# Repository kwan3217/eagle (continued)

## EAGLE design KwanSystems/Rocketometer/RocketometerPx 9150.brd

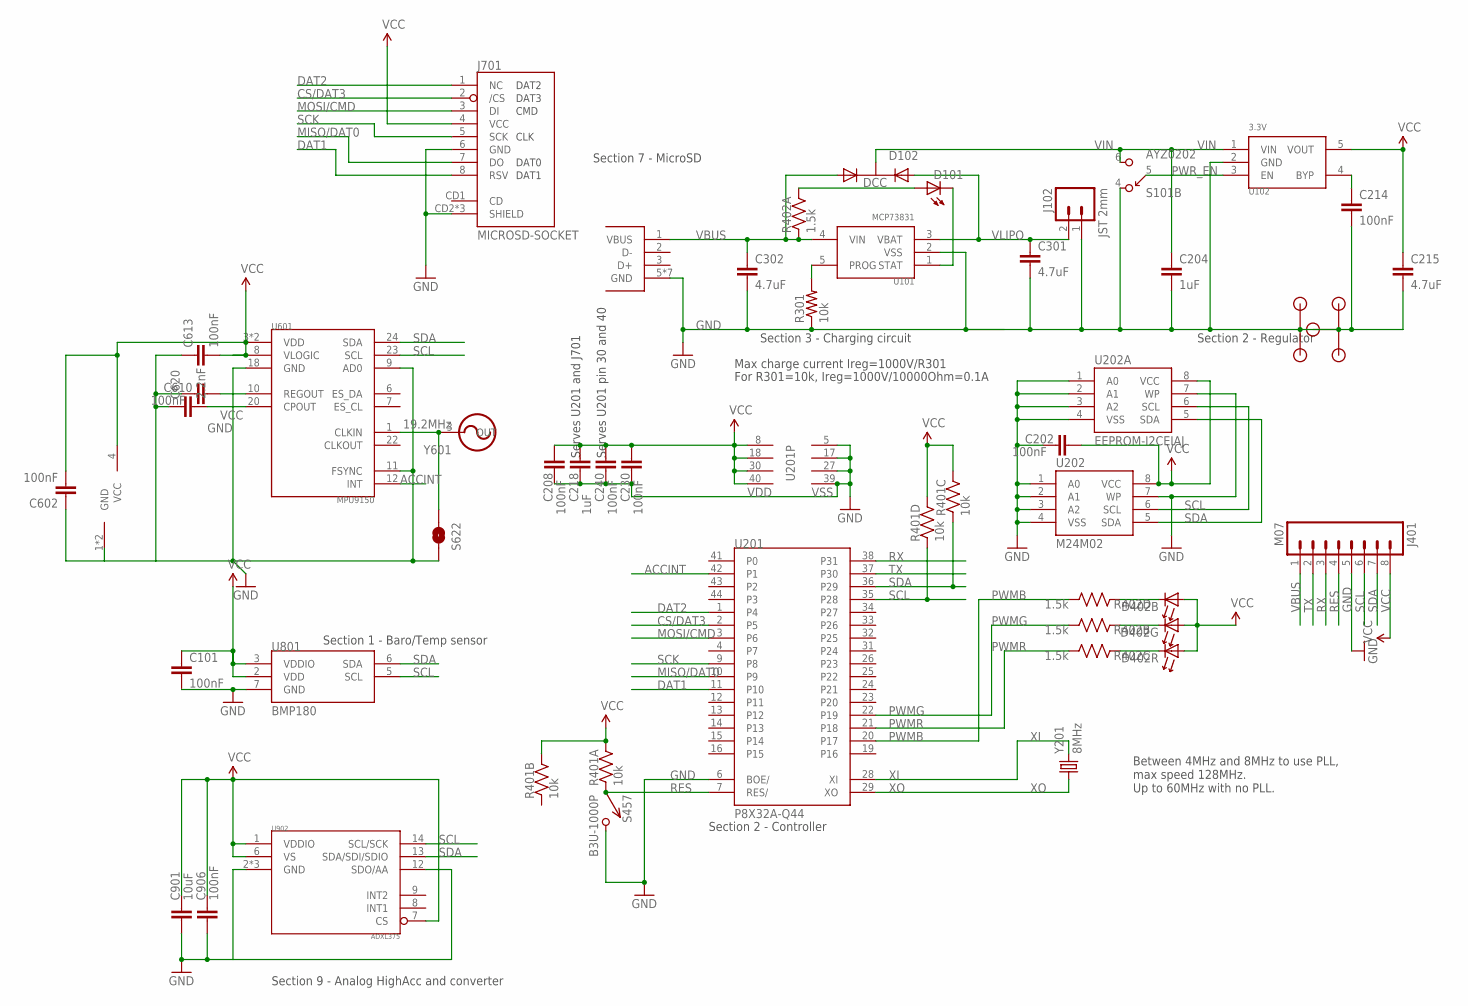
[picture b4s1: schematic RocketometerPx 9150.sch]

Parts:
C101, C202, C208, C214, C230, C240, C602, C610, C613: 100nF; 0402-CAP; DIGIKEY 445-1265-1-ND
C204, C218: 1uF; 0402-CAP; DIGIKEY 445-4114-1-ND
C215, C301, C302: 4.7uF; 0402-CAP; DIGIKEY 445-7395-1-ND
C620: 2.2nF; 0402-CAP; DIGIKEY 445-1257-1-ND
C901: 10uF; 0603-CAP; DIGIKEY 445-7486-1-ND
C906: 100nF; 0402-CAP; DIGIKEY 445-1317-2-ND
D101: YELLOW; LED-0603; DIGIKEY 350-2032-1-ND
D102: DCC; SOT-23-3; DIGIKEY 568-6500-1-ND
D402: SMLP36RGB2W(R); SMLP36
J101: USB_MICROB_JSTGCT; USB_MICROB_3075; DIGIKEY 455-2562-1-ND
J102: JST 2mm; JST-2-SMD; DIGIKEY 455-1749-1-ND
J401: M07; 1X08; DIGIKEY $NOPART
J701: MICROSD-SOCKET; MICROSD-SOCKET-PP; DIGIKEY 101-00581-59-1-ND
JP1, JP2, JP3, JP4, JP5: STANDOFF; DIGIKEY $NOPART
R301: 10k; 0402-RES; DIGIKEY P10.0KLCT-ND
R401: 10k; CRA04; DIGIKEY CRA4S810KCT-ND
R402: 1.5k; CRA04; DIGIKEY CRA4S81.5KCT-ND
S101: AYZ0202; DIGIKEY 401-2013-1-ND
S457: B3U-1000P; DIGIKEY SW1020CT-ND
S622: SOLDERJUMPERNO; SJ_2S-NO; DIGIKEY $NOPART
U101: MCP73831; SOT-23-5; DIGIKEY 576-1910-1-ND
U102: 3.3V; SOT-23-5; DIGIKEY 576-1910-1-ND
U201: P8X32A-Q44; DIGIKEY P8X32A-Q44-ND
U202: M24M02; SO8N; DIGIKEY 497-11600-1-ND
U202A: EEPROM-I2CEIAJ; SO08-EIAJ; DIGIKEY $NOPART
U601: MPU9150; MPU60X0; DIGIKEY $NOPART
U801: BMP180; DIGIKEY 828-1027-1-ND
U902: ADXL375
Y201: 8MHz; CRYSTAL_SMD_3_2MM_2_5MM; DIGIKEY 644-1178-1-ND
Y601: 19.2MHz; CRYSTAL_SMD_5MM_3_2MM

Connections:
ACCINT: U201.42 (P1), U601.12 (INT)
CS/DAT3: J701.2 (/CS), U201.2 (P5)
DAT1: J701.8 (RSV), U201.11 (P10)
DAT2: J701.1 (NC), U201.1 (P4)
GND: C101.2, C202.2, C204.2, C208.2, C214.2, C215.2, C218.2, C230.2, C240.2, C301.2, C302.2, C602.1, C610.2, C613.1, C620.1, C901.2, C906.2, J101.5 (GND), J101.P$1 (GND), J101.P$2 (GND), J101.P$3 (GND), J101.P$4 (GND), J101.P$8 (GND), J101.P$10 (GND), J102.1, J401.5, J701.6 (GND), J701.CD2 (SHIELD), J701.GND1 (SHIELD), J701.GND3 (SHIELD), JP1.P$1, JP2.P$1, JP3.P$1, JP4.P$1, JP5.P$1, R301.1, S101.4, S457.P$2 (2), S622.2, U101.2 (VSS), U102.2 (GND), U201.5 (VSS), U201.6 (BOE/), U201.17 (VSS), U201.27 (VSS), U201.39 (VSS), U202.1 (A0), U202.2 (A1), U202.3 (A2), U202.4 (VSS), U202.7 (WP), U202A.1 (A0), U202A.2 (A1), U202A.3 (A2), U202A.4 (VSS), U202A.7 (WP), U601.9 (AD0), U601.11 (FSYNC), U601.18 (GND), U801.7 (GND), U902.2 (GND), U902.4 (GND), U902.5 (GND), U902.12 (SDO/AA), Y601.1 (GND), Y601.2 (GND)
MISO/DAT0: J701.7 (DO), U201.10 (P9)
MOSI/CMD: J701.3 (DI), U201.3 (P6)
unnamed: C620.2, U601.20 (CPOUT)
unnamed: R301.2, U101.5 (PROG)
unnamed: S622.1, U601.1 (CLKIN), Y601.3 (OUT)
unnamed: D101.C, U101.1 (STAT)
unnamed: D101.A, R402.8 (2)
unnamed: C610.1, U601.10 (REGOUT)
unnamed: C214.1, U102.4 (BYP)
PWMB: R402.4 (1), U201.20 (P17)
PWMG: R402.2 (1), U201.22 (P19)
PWMR: R402.3 (1), U201.21 (P18)
PWR_EN: S101.5, U102.3 (EN)
QWMB: D402.3 (C), R402.6 (2)
QWMG: D402.5 (C), R402.7 (2)
QWMR: D402.1 (C), R402.5 (2)
RES: J401.4, R401.1, S457.P$1 (1), U201.7 (RES/)
RX: J401.3, U201.38 (P31)
SCK: J701.5 (SCK), U201.9 (P8)
SCL: J401.6, R401.4 (1), U201.35 (P28), U202.6 (SCL), U202A.6 (SCL), U601.23 (SCL), U801.5 (SCL), U902.14 (SCL/SCK)
SDA: J401.7, R401.3 (1), U201.36 (P29), U202.5 (SDA), U202A.5 (SDA), U601.24 (SDA), U801.6 (SDA), U902.13 (SDA/SDI/SDIO)
TX: J401.2, U201.37 (P30)
VBUS: C302.1, D102.1 (A1), J101.1 (VBUS), J401.1, R402.1, U101.4 (VIN)
VCC: C101.1, C202.1, C208.1, C215.1, C218.1, C230.1, C240.1, C602.2, C613.2, C901.1, C906.1, D402.2 (A), D402.4 (A), D402.6 (A), J401.8, J701.4 (VCC), R401.5 (2), R401.6 (2), R401.7 (2), R401.8 (2), U102.5 (VOUT), U201.8 (VDD), U201.18 (VDD), U201.30 (VDD), U201.40 (VDD), U202.8 (VCC), U202A.8 (VCC), U601.3 (VDD), U601.8 (VLOGIC), U601.13 (VDD), U801.2 (VDD), U801.3 (VDDIO), U902.1 (VDDIO), U902.6 (VS), U902.7 (CS), Y601.4 (VCC)
VIN: C204.1, D102.3 (K), S101.6, U102.1 (VIN)
VLIPO: C301.1, D102.2 (A2), J102.2, U101.3 (VBAT)
XI: U201.28 (XI), Y201.2
XO: U201.29 (XO), Y201.1

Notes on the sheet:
Section 2 - Regulator
Section 3 - Charging circuit
Section 7 - MicroSD
Section 1 - Baro/Temp sensor
Max charge current Ireg=1000V/R301
For R301=10k, Ireg=1000V/10000Ohm=0.1A
Section 2 - Controller
Serves U201 and J701
Serves U201 pin 30 and 40
Between 4MHz and 8MHz to use PLL, max speed 128MHz. Up to 60MHz with no PLL.
Section 9 - Analog HighAcc and converter

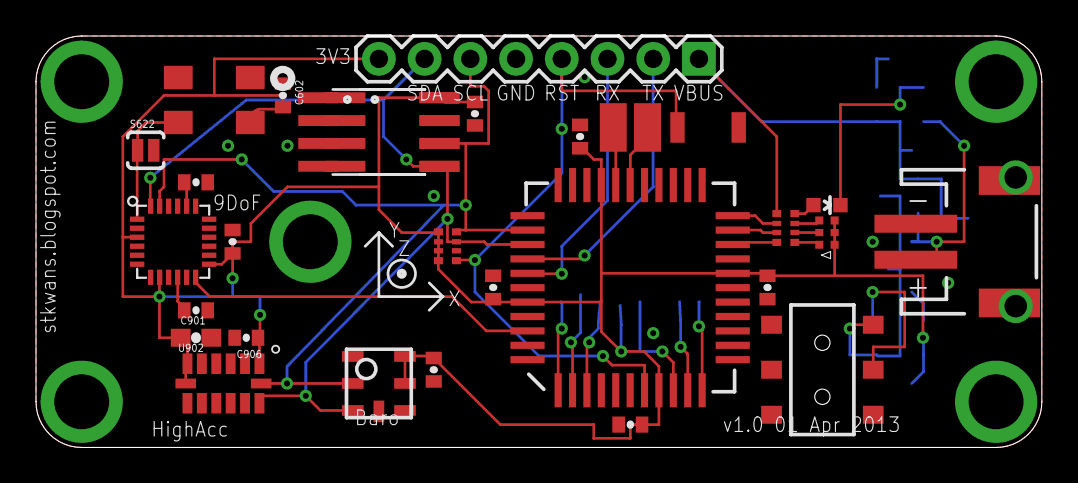
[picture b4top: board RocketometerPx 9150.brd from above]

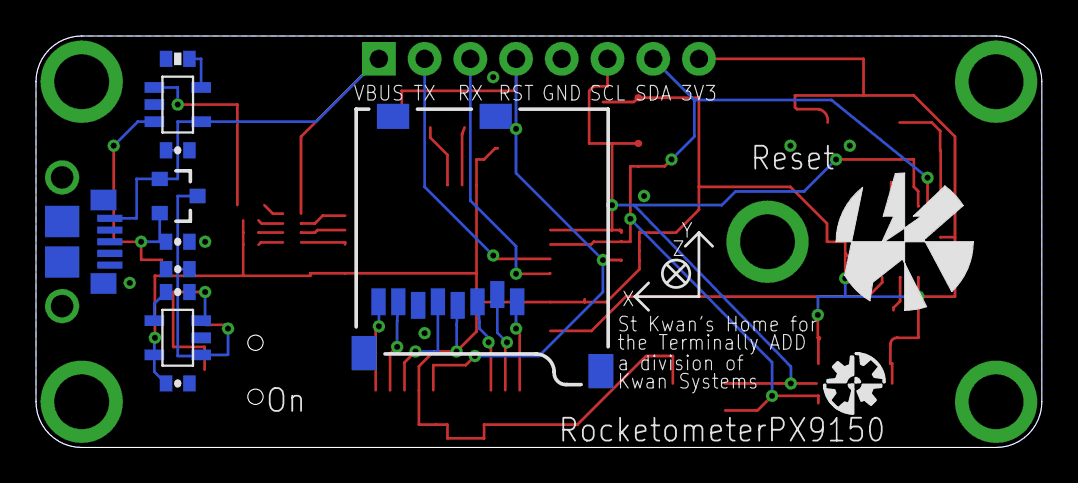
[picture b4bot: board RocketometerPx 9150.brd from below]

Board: 2 copper layers, 55.9 x 22.9 mm, 48 parts (13 on the bottom side), 33 nets.

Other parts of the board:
U$4: AXES
U$5: KWAN_ACC
U$6: OSHW_ACC

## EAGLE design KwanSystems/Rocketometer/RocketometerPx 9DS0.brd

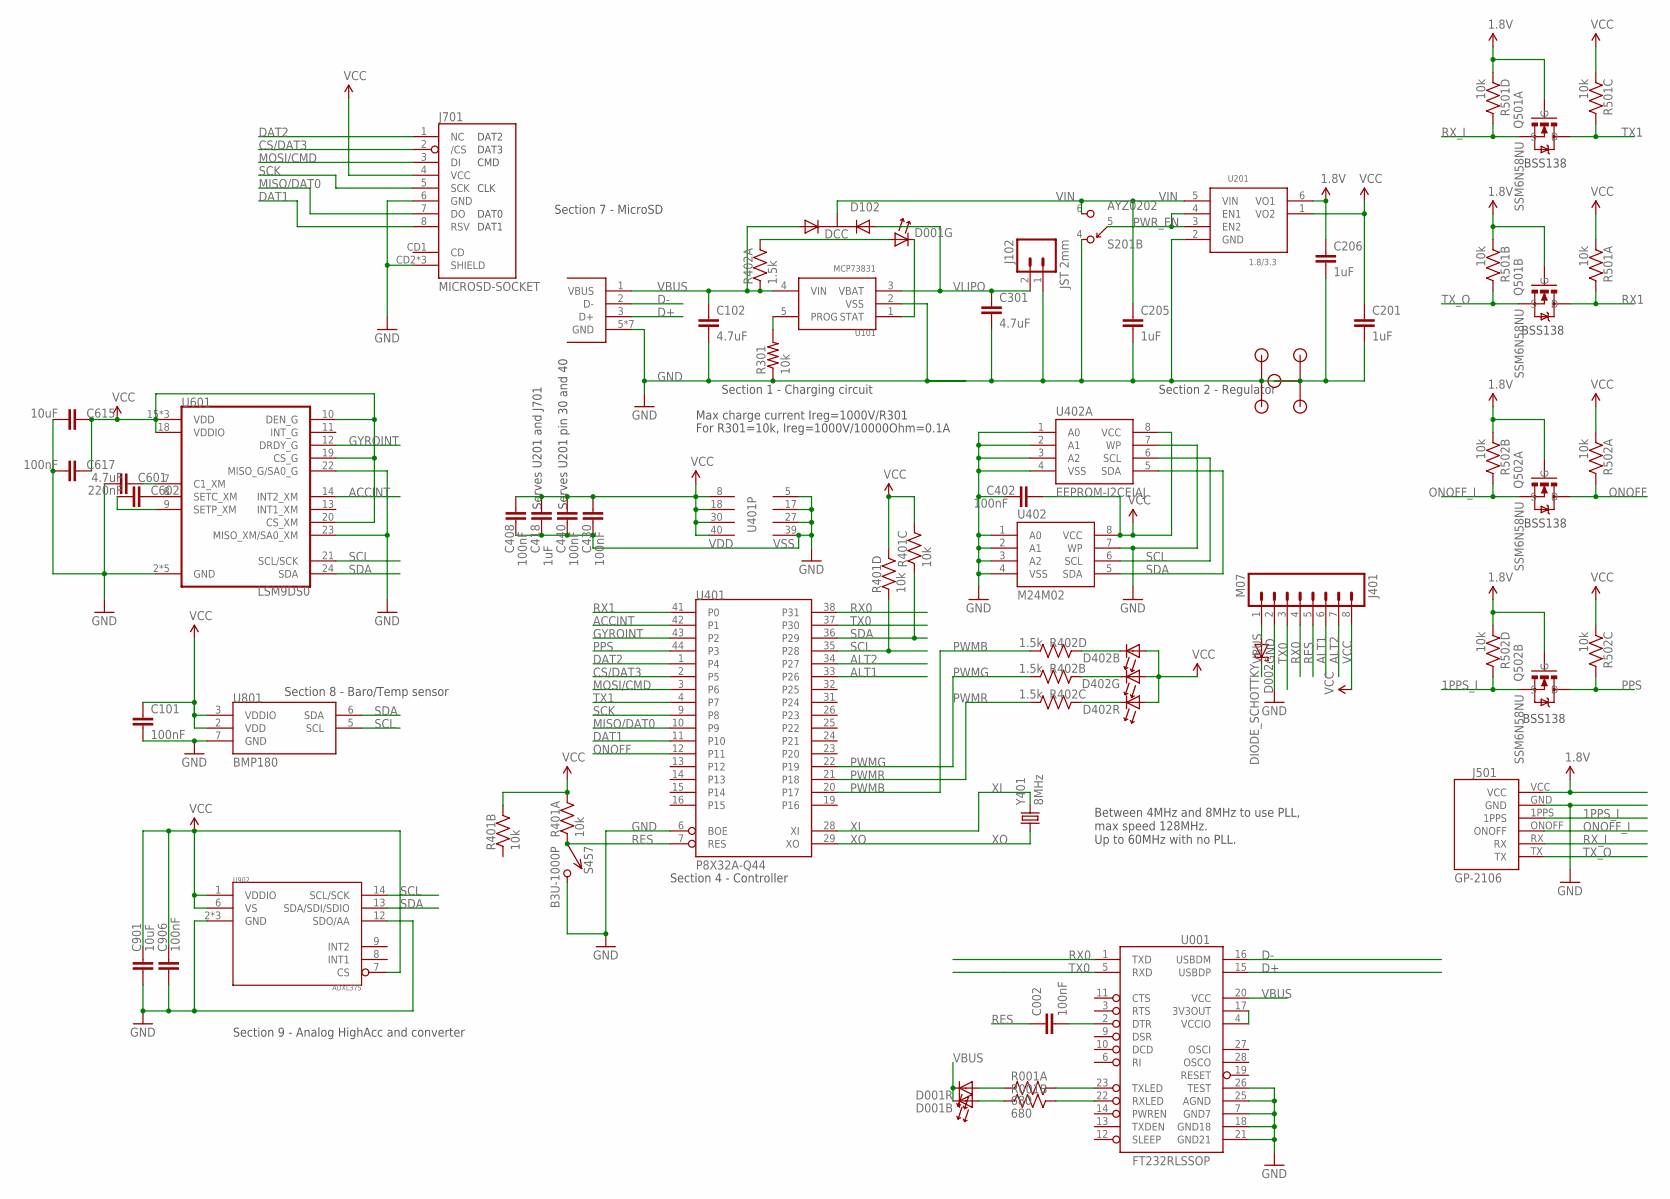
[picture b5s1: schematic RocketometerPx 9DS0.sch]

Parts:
C002: 100nF; 0402-CAP; DIGIKEY 445-1268-1-ND
C101, C402, C408, C430, C440, C617: 100nF; 0402-CAP; DIGIKEY 445-1265-1-ND
C102, C301, C601: 4.7uF; 0402-CAP; DIGIKEY 445-7395-1-ND
C201: 1uF; 0402-CAP; DIGIKEY 445-7395-1-ND
C205, C418: 1uF; 0402-CAP; DIGIKEY 445-4114-1-ND
C206: 1uF; 0402-CAP; DIGIKEY 445-1265-1-ND
C602: 220nF; 0402-CAP; DIGIKEY 445-1265-1-ND
C615, C901: 10uF; 0603-CAP; DIGIKEY 445-7486-1-ND
C906: 100nF; 0402-CAP; DIGIKEY 445-1317-2-ND
D001, D402: SMLP36RGB2W(R); SMLP36
D002: DIODE_SCHOTTKY; D0603
D102: DCC; SOT-23-3; DIGIKEY 568-6500-1-ND
J001: USB_MICROB_JSTFCI; USB-MICROB-CONN-09505; DIGIKEY 455-2562-1-ND
J102: JST 2mm; JST-2-SMD; DIGIKEY 455-1749-1-ND
J401: M07; M08SIP; DIGIKEY $NOPART
J501: GP-2106
J701: MICROSD-SOCKET; MICROSD-SOCKET-PP; DIGIKEY 101-00581-59-1-ND
JP1, JP2, JP3, JP4, JP5: STANDOFF; DIGIKEY $NOPART
Q501, Q502: SSM6N58NU; UDFN6
R001: 680; CRA02; DIGIKEY CRA4S8680CT-ND
R301: 10k; 0402-RES; DIGIKEY P10.0KLCT-ND
R401, R501, R502: 10k; CRA04; DIGIKEY CRA4S810KCT-ND
R402: 1.5k; CRA04; DIGIKEY CRA4S81.5KCT-ND
S201: AYZ0202; DIGIKEY 401-2013-1-ND
S457: B3U-1000P; DIGIKEY SW1020CT-ND
U001: FT232RLSSOP; SSOP28DB; DIGIKEY 768-1007-1-ND
U101: MCP73831; SOT-23-5; DIGIKEY 576-1910-1-ND
U201: 1.8/3.3; SOT-23-6
U401: P8X32A-Q44; DIGIKEY P8X32A-Q44-ND
U402: M24M02; SO8N; DIGIKEY 497-11600-1-ND
U402A: EEPROM-I2CEIAJ; SO08-EIAJ; DIGIKEY $NOPART
U601: LSM9DS0; LGA24_LSM
U801: BMP180; DIGIKEY 828-1027-1-ND
U902: ADXL375
Y401: 8MHz; CRYSTAL_SMD_3_2MM_2_5MM; DIGIKEY 644-1178-1-ND

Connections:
1.8V: C206.1, J501.VCC, Q501.2 (G), Q501.5 (G), Q502.2 (G), Q502.5 (G), R501.2 (1), R501.4 (1), R502.2 (1), R502.4 (1), U201.6 (VO1)
1PPS_I: J501.1PPS, Q502.4 (S), R502.5 (2)
ACCINT: U401.42 (P1), U601.14 (INT2_XM)
ALT1: J401.6, U401.33 (P26)
ALT2: J401.7, U401.34 (P27)
CS/DAT3: J701.2 (/CS), U401.2 (P5)
D+: J001.3 (D+), U001.15 (USBDP)
D-: J001.2 (D-), U001.16 (USBDM)
DAT1: J701.8 (RSV), U401.11 (P10)
DAT2: J701.1 (NC), U401.1 (P4)
DTR#: C002.2, U001.2 (DTR)
GND: C101.2, C102.2, C201.2, C205.2, C206.2, C301.2, C402.2, C408.2, C418.2, C430.2, C440.2, C601.2, C615.1, C617.1, C901.2, C906.2, J001.5 (GND), J001.P1 (GND), J001.P2 (GND), J001.P3 (GND), J001.P4 (GND), J001.P5 (GND), J001.P6 (GND), J102.1, J401.2, J501.GND, J701.6 (GND), J701.CD2 (SHIELD), J701.GND1 (SHIELD), J701.GND3 (SHIELD), JP1.P$1, JP2.P$1, JP3.P$1, JP4.P$1, JP5.P$1, R301.1, S201.4, S457.P$2 (2), U001.7 (GND7), U001.18 (GND18), U001.21 (GND21), U001.25 (AGND), U001.26 (TEST), U101.2 (VSS), U201.2 (GND), U401.5 (VSS), U401.6 (BOE), U401.17 (VSS), U401.27 (VSS), U401.39 (VSS), U402.1 (A0), U402.2 (A1), U402.3 (A2), U402.4 (VSS), U402.7 (WP), U402A.1 (A0), U402A.2 (A1), U402A.3 (A2), U402A.4 (VSS), U402A.7 (WP), U601.2 (GND), U601.3 (GND), U601.4 (GND), U601.5 (GND), U601.6 (GND), U601.22 (MISO_G/SA0_G), U601.23 (MISO_XM/SA0_XM), U801.7 (GND), U902.2 (GND), U902.4 (GND), U902.5 (GND), U902.12 (SDO/AA)
GYROINT: U401.43 (P2), U601.12 (DRDY_G)
MISO/DAT0: J701.7 (DO), U401.10 (P9)
MOSI/CMD: J701.3 (DI), U401.3 (P6)
unnamed: U001.4 (VCCIO), U001.17 (3V3OUT)
unnamed: R301.2, U101.5 (PROG)
unnamed: C601.1, U601.7 (C1_XM)
unnamed: D001.5 (C), U101.1 (STAT)
unnamed: D001.6 (A), R402.8 (2)
unnamed: C602.1, U601.8 (SETC_XM)
unnamed: C602.2, U601.9 (SETP_XM)
unnamed: D001.4 (A), R001.1
unnamed: D001.2 (A), R001.2 (1)
ONOFF: Q502.6 (D), R502.8 (2), U401.12 (P11)
ONOFF_I: J501.ONOFF, Q502.1 (S), R502.7 (2)
PPS: Q502.3 (D), R502.6 (2), U401.44 (P3)
PWMB: R402.4 (1), U401.20 (P17)
PWMG: R402.2 (1), U401.22 (P19)
PWMR: R402.3 (1), U401.21 (P18)
PWR_EN: S201.5, U201.3 (EN2), U201.4 (EN1)
QWMB: D402.3 (C), R402.6 (2)
QWMG: D402.5 (C), R402.7 (2)
QWMR: D402.1 (C), R402.5 (2)
RES: C002.1, J401.5, R401.1, S457.P$1 (1), U401.7 (RES)
RX0: J401.4, U001.1 (TXD), U401.38 (P31)
RX1: Q501.3 (D), R501.8 (2), U401.41 (P0)
RXLED1: R001.3 (2), U001.22 (RXLED)
RX_I: J501.RX, Q501.1 (S), R501.5 (2)
SCK: J701.5 (SCK), U401.9 (P8)
SCL: R401.4 (1), U401.35 (P28), U402.6 (SCL), U402A.6 (SCL), U601.21 (SCL/SCK), U801.5 (SCL), U902.14 (SCL/SCK)
SDA: R401.3 (1), U401.36 (P29), U402.5 (SDA), U402A.5 (SDA), U601.24 (SDA), U801.6 (SDA), U902.13 (SDA/SDI/SDIO)
TX0: J401.3, U001.5 (RXD), U401.37 (P30)
TX1: Q501.6 (D), R501.6 (2), U401.4 (P7)
TXLED1: R001.4 (2), U001.23 (TXLED)
TX_O: J501.TX, Q501.4 (S), R501.7 (2)
VBUS: C102.1, D001.1 (C), D001.3 (C), D002.C (K), D102.1 (A1), J001.1 (VBUS), R402.1, U001.20 (VCC), U101.4 (VIN)
VBUS+: D002.A, J401.1
VCC: C101.1, C201.1, C402.1, C408.1, C418.1, C430.1, C440.1, C615.2, C617.2, C901.1, C906.1, D402.2 (A), D402.4 (A), D402.6 (A), J401.8, J701.4 (VCC), R401.5 (2), R401.6 (2), R401.7 (2), R401.8 (2), R501.1, R501.3 (1), R502.1, R502.3 (1), U201.1 (VO2), U401.8 (VDD), U401.18 (VDD), U401.30 (VDD), U401.40 (VDD), U402.8 (VCC), U402A.8 (VCC), U601.10 (DEN_G), U601.15 (VDD), U601.16 (VDD), U601.17 (VDD), U601.18 (VDDIO), U601.19 (CS_G), U601.20 (CS_XM), U801.2 (VDD), U801.3 (VDDIO), U902.1 (VDDIO), U902.6 (VS), U902.7 (CS)
VIN: C205.1, D102.3 (K), S201.6, U201.5 (VIN)
VLIPO: C301.1, D102.2 (A2), J102.2, U101.3 (VBAT)
XI: U401.28 (XI), Y401.2
XO: U401.29 (XO), Y401.1

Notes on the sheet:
Section 2 - Regulator
Section 1 - Charging circuit
Section 7 - MicroSD
Section 8 - Baro/Temp sensor
Max charge current Ireg=1000V/R301
For R301=10k, Ireg=1000V/10000Ohm=0.1A
Section 4 - Controller
Serves U201 and J701
Serves U201 pin 30 and 40
Between 4MHz and 8MHz to use PLL, max speed 128MHz. Up to 60MHz with no PLL.
Section 9 - Analog HighAcc and converter
BSS138

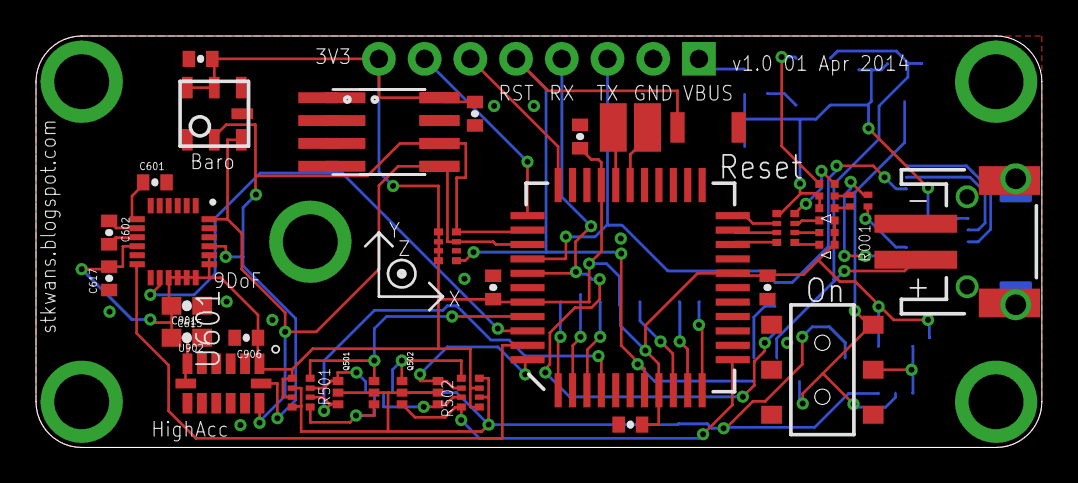
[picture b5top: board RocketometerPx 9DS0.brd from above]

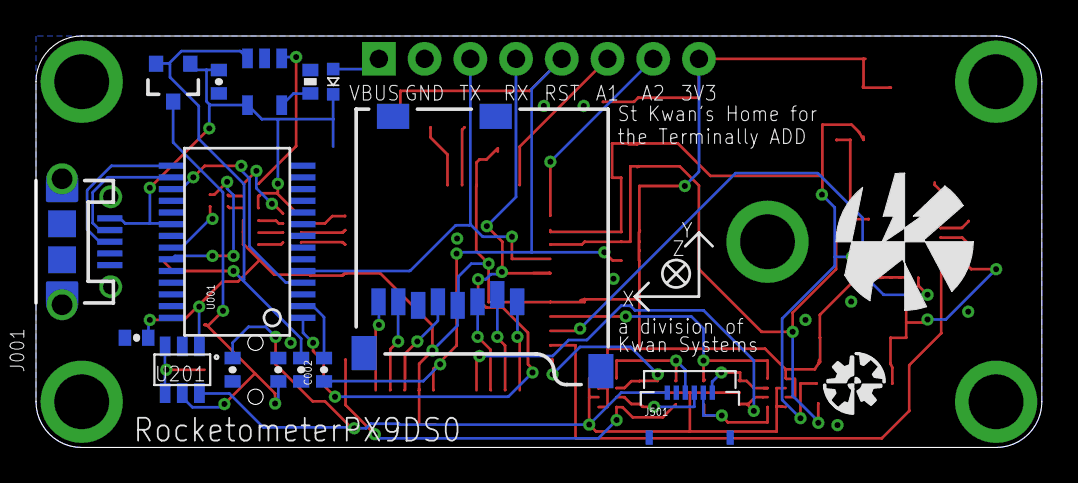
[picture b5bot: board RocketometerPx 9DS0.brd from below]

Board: 2 copper layers, 55.9 x 22.9 mm, 55 parts (17 on the bottom side), 53 nets.

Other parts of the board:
U$4: AXES
U$5: KWAN_ACC
U$6: OSHW_ACC

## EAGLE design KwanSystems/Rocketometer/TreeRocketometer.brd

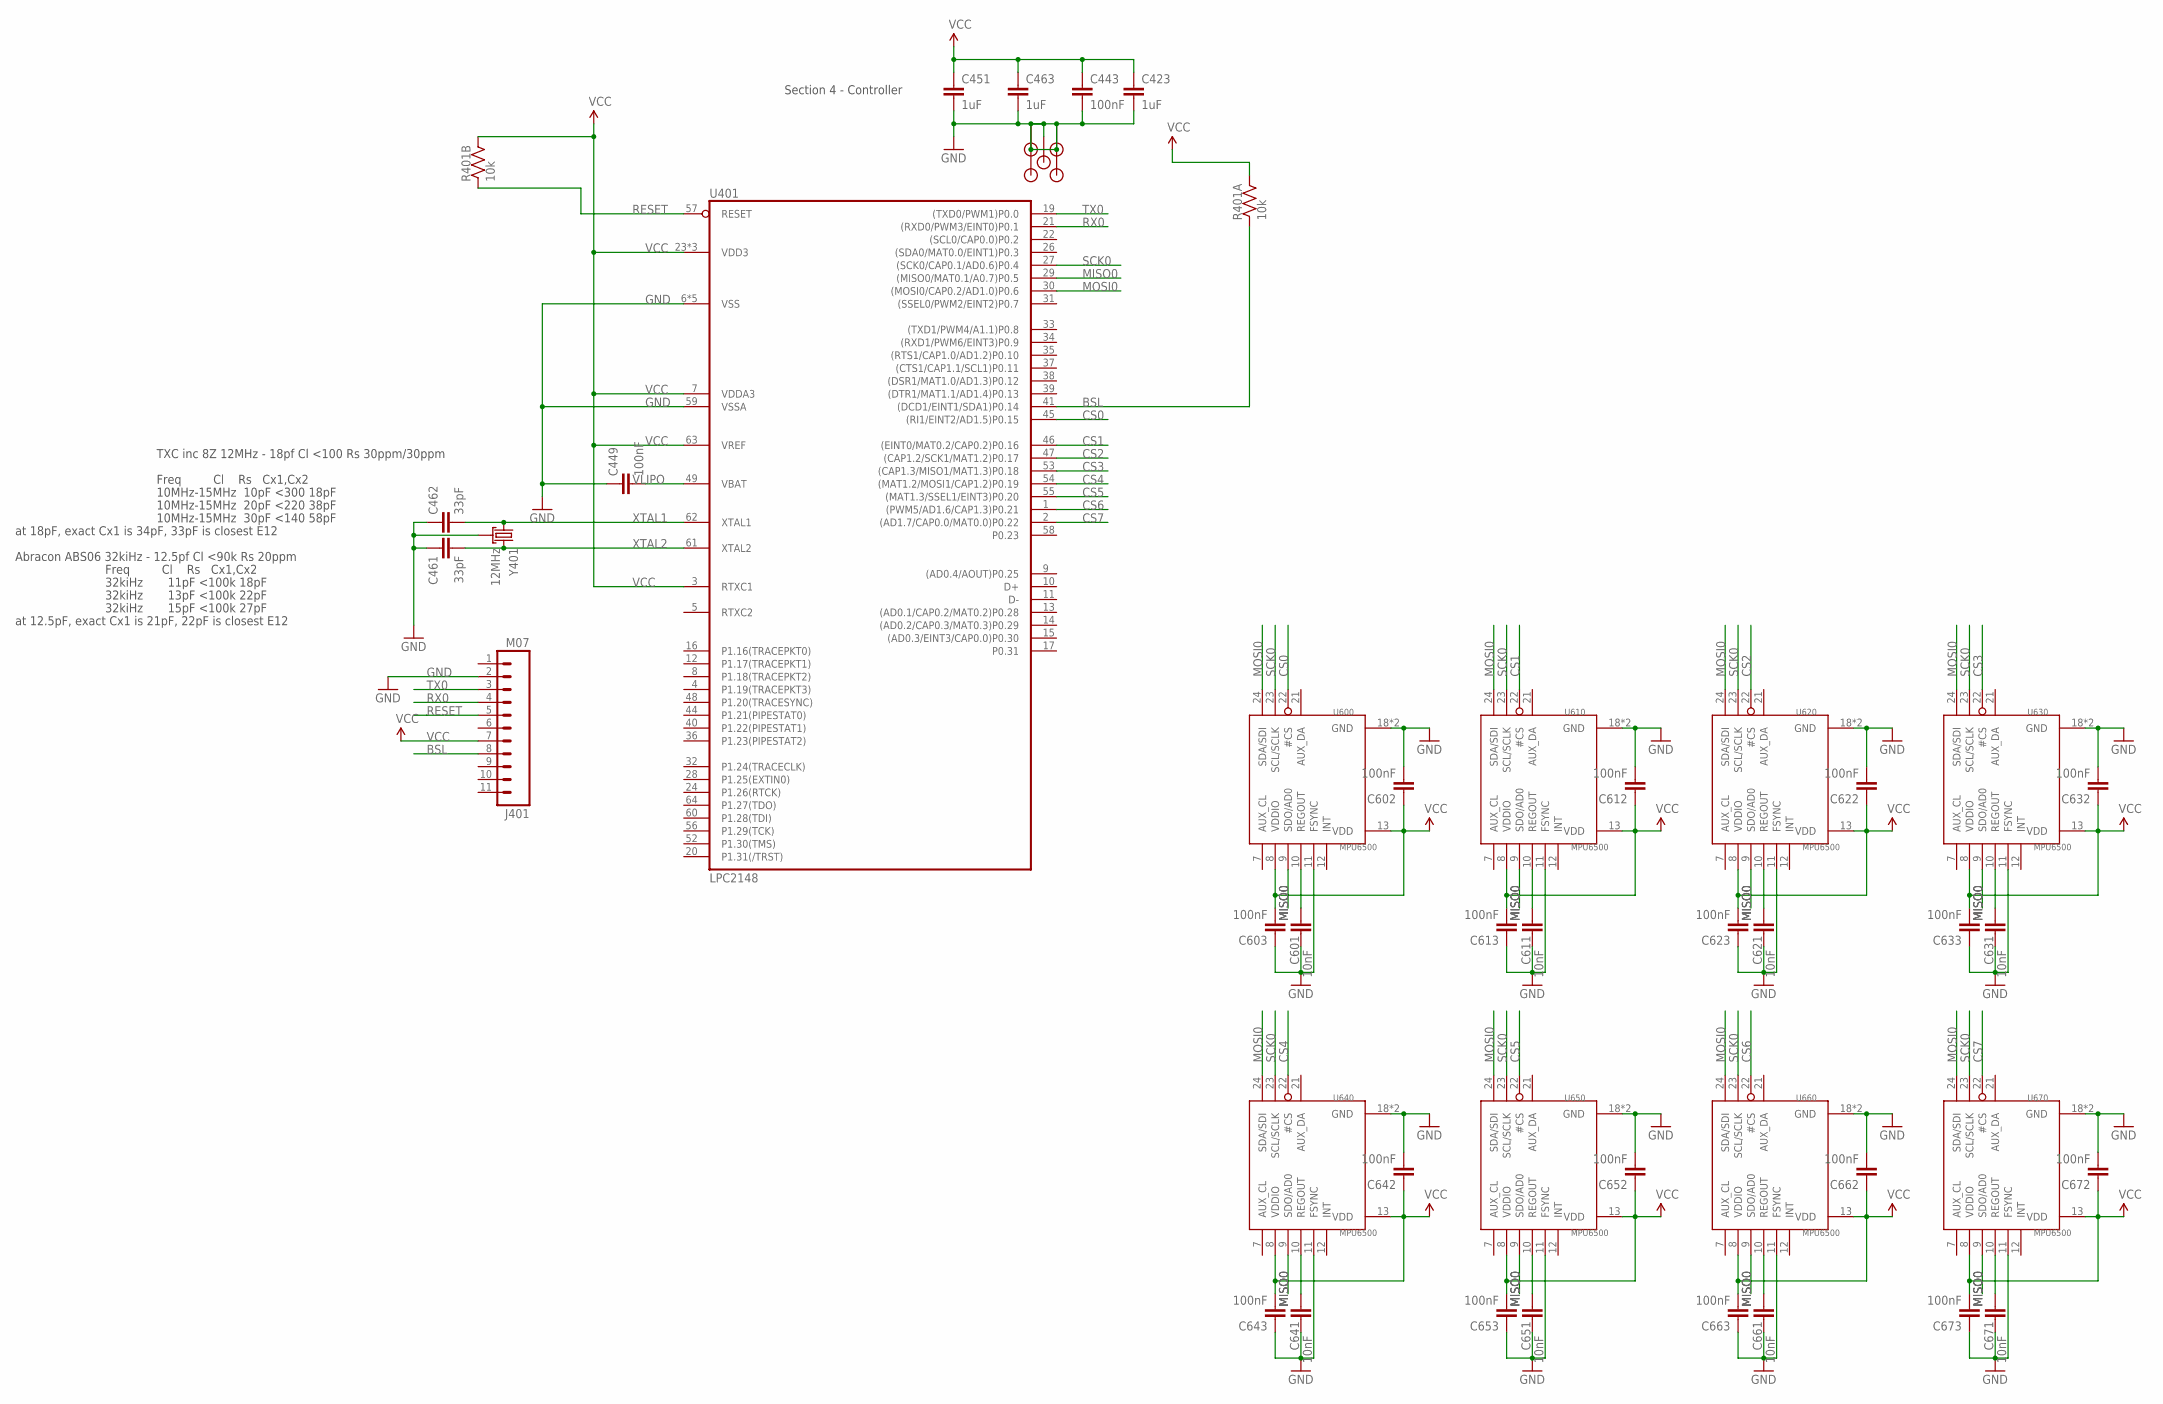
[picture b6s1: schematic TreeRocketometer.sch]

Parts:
C423, C451, C463: 1uF; 0402-CAP; DIGIKEY 445-4114-1-ND
C443, C449, C602, C603, C612, C613, C622, C623, C632, C633, C642, C643, C652, C653, C662, C663, C672, C673: 100nF; 0402-CAP; DIGIKEY 445-1265-1-ND
C461, C462: 33pF; 0402-CAP; DIGIKEY 445-1241-1-ND
C601, C611, C621, C631, C641, C651, C661, C671: 10nF; 0402-CAP; DIGIKEY 445-1265-1-ND
J401: M07; 1X11; DIGIKEY $NOPART
JP1, JP2, JP3, JP4, JP5: STANDOFF; DIGIKEY $NOPART
R401: 10k; CRA04; DIGIKEY CRA4S810KCT-ND
U401: LPC2148; LQFP64
U600, U610, U620, U630, U640, U650, U660, U670: MPU6500; QFN24
Y401: 12MHz; CRYSTAL_SMD_2MM_2_5MM; DIGIKEY 887-1487-1-ND

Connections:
BSL: J401.8, R401.1, U401.41 ((DCD1/EINT1/SDA1)P0.14)
CS0: U401.45 ((RI1/EINT2/AD1.5)P0.15), U600.22 (#CS)
CS1: U401.46 ((EINT0/MAT0.2/CAP0.2)P0.16), U610.22 (#CS)
CS2: U401.47 ((CAP1.2/SCK1/MAT1.2)P0.17), U620.22 (#CS)
CS3: U401.53 ((CAP1.3/MISO1/MAT1.3)P0.18), U630.22 (#CS)
CS4: U401.54 ((MAT1.2/MOSI1/CAP1.2)P0.19), U640.22 (#CS)
CS5: U401.55 ((MAT1.3/SSEL1/EINT3)P0.20), U650.22 (#CS)
CS6: U401.1 ((PWM5/AD1.6/CAP1.3)P0.21), U660.22 (#CS)
CS7: U401.2 ((AD1.7/CAP0.0/MAT0.0)P0.22), U670.22 (#CS)
GND: C423.2, C443.2, C449.1, C451.2, C461.1, C462.1, C463.2, C601.2, C602.2, C603.1, C611.2, C612.2, C613.1, C621.2, C622.2, C623.1, C631.2, C632.2, C633.1, C641.2, C642.2, C643.1, C651.2, C652.2, C653.1, C661.2, C662.2, C663.1, C671.2, C672.2, C673.1, J401.2, JP1.P$1, JP2.P$1, JP3.P$1, JP4.P$1, JP5.P$1, U401.6 (VSS), U401.18 (VSS), U401.25 (VSS), U401.42 (VSS), U401.50 (VSS), U401.59 (VSSA), U600.11 (FSYNC), U600.18 (GND), U600.20 (GND), U610.11 (FSYNC), U610.18 (GND), U610.20 (GND), U620.11 (FSYNC), U620.18 (GND), U620.20 (GND), U630.11 (FSYNC), U630.18 (GND), U630.20 (GND), U640.11 (FSYNC), U640.18 (GND), U640.20 (GND), U650.11 (FSYNC), U650.18 (GND), U650.20 (GND), U660.11 (FSYNC), U660.18 (GND), U660.20 (GND), U670.11 (FSYNC), U670.18 (GND), U670.20 (GND), Y401.2 (GND), Y401.4 (GND)
MISO0: U401.29 ((MISO0/MAT0.1/A0.7)P0.5), U600.9 (SDO/AD0), U610.9 (SDO/AD0), U620.9 (SDO/AD0), U630.9 (SDO/AD0), U640.9 (SDO/AD0), U650.9 (SDO/AD0), U660.9 (SDO/AD0), U670.9 (SDO/AD0)
MOSI0: U401.30 ((MOSI0/CAP0.2/AD1.0)P0.6), U600.24 (SDA/SDI), U610.24 (SDA/SDI), U620.24 (SDA/SDI), U630.24 (SDA/SDI), U640.24 (SDA/SDI), U650.24 (SDA/SDI), U660.24 (SDA/SDI), U670.24 (SDA/SDI)
unnamed: C611.1, U610.10 (REGOUT)
unnamed: C621.1, U620.10 (REGOUT)
unnamed: C601.1, U600.10 (REGOUT)
unnamed: C631.1, U630.10 (REGOUT)
unnamed: C641.1, U640.10 (REGOUT)
unnamed: C651.1, U650.10 (REGOUT)
unnamed: C661.1, U660.10 (REGOUT)
unnamed: C671.1, U670.10 (REGOUT)
RESET: J401.5, R401.2 (1), U401.57 (RESET)
RX0: J401.4, U401.21 ((RXD0/PWM3/EINT0)P0.1)
SCK0: U401.27 ((SCK0/CAP0.1/AD0.6)P0.4), U600.23 (SCL/SCLK), U610.23 (SCL/SCLK), U620.23 (SCL/SCLK), U630.23 (SCL/SCLK), U640.23 (SCL/SCLK), U650.23 (SCL/SCLK), U660.23 (SCL/SCLK), U670.23 (SCL/SCLK)
TX0: J401.3, U401.19 ((TXD0/PWM1)P0.0)
VCC: C423.1, C443.1, C451.1, C463.1, C602.1, C603.2, C612.1, C613.2, C622.1, C623.2, C632.1, C633.2, C642.1, C643.2, C652.1, C653.2, C662.1, C663.2, C672.1, C673.2, J401.7, R401.7 (2), R401.8 (2), U401.3 (RTXC1), U401.7 (VDDA3), U401.23 (VDD3), U401.43 (VDD3), U401.51 (VDD3), U401.63 (VREF), U600.8 (VDDIO), U600.13 (VDD), U610.8 (VDDIO), U610.13 (VDD), U620.8 (VDDIO), U620.13 (VDD), U630.8 (VDDIO), U630.13 (VDD), U640.8 (VDDIO), U640.13 (VDD), U650.8 (VDDIO), U650.13 (VDD), U660.8 (VDDIO), U660.13 (VDD), U670.8 (VDDIO), U670.13 (VDD)
VLIPO: C449.2, U401.49 (VBAT)
XTAL1: C462.2, U401.62 (XTAL1), Y401.1
XTAL2: C461.2, U401.61 (XTAL2), Y401.3 (2)

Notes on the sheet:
Section 4 - Controller
Freq Cl Rs Cx1,Cx2
10MHz-15MHz 10pF <300 18pF
10MHz-15MHz 20pF <220 38pF
10MHz-15MHz 30pF <140 58pF
TXC inc 8Z 12MHz - 18pf Cl <100 Rs 30ppm/30ppm
at 18pF, exact Cx1 is 34pF, 33pF is closest E12
32kiHz 11pF <100k 18pF
32kiHz 13pF <100k 22pF
32kiHz 15pF <100k 27pF
Abracon ABS06 32kiHz - 12.5pf Cl <90k Rs 20ppm
at 12.5pF, exact Cx1 is 21pF, 22pF is closest E12

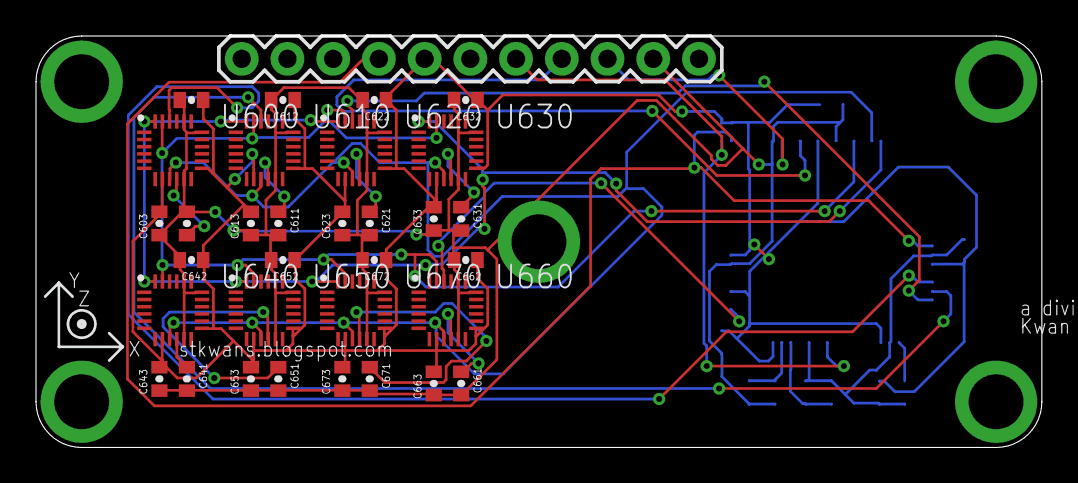
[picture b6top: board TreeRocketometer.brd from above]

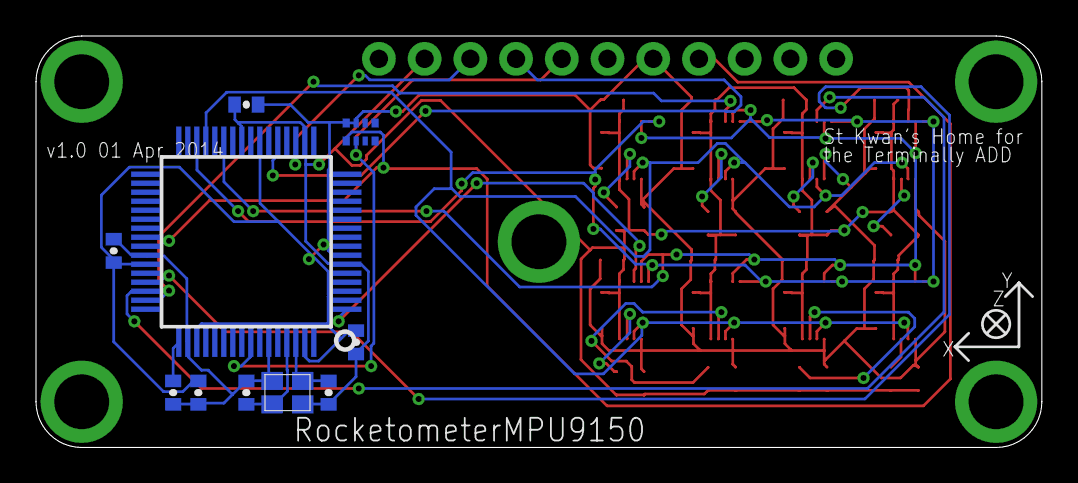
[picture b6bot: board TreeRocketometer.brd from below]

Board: 2 copper layers, 55.9 x 22.9 mm, 49 parts (10 on the bottom side), 28 nets.

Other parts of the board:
U$4: AXES
